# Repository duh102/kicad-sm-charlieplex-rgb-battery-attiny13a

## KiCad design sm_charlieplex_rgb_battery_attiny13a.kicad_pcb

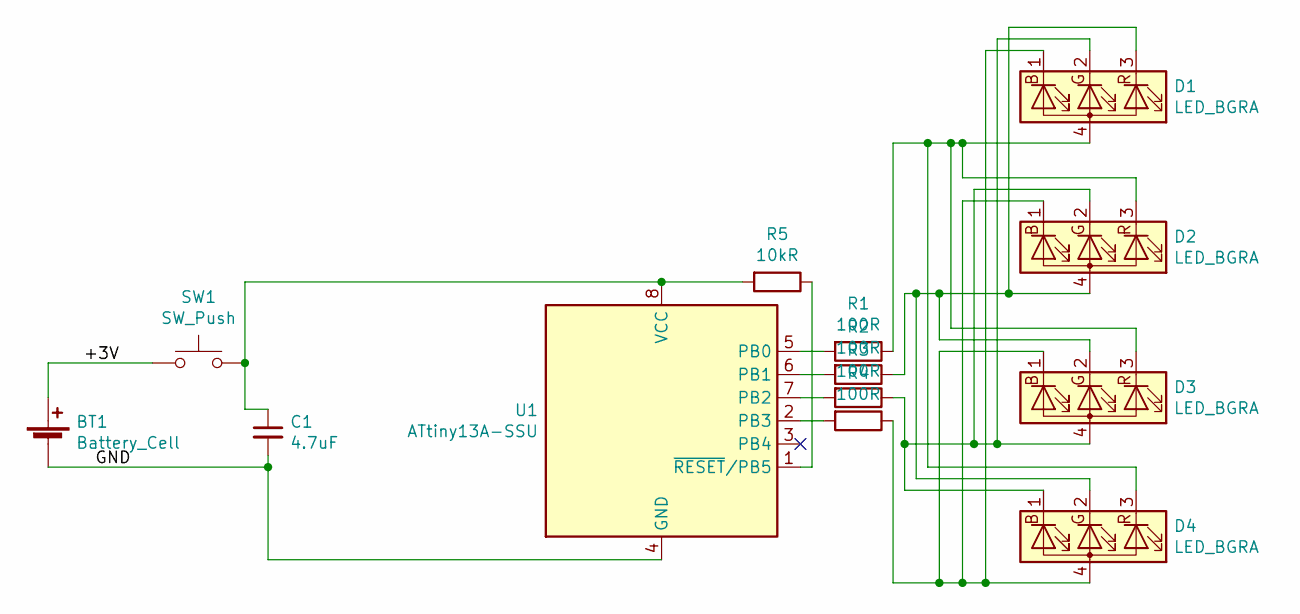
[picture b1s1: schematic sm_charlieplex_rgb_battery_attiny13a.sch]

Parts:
BT1: Battery_Cell; BatteryHolder_Keystone_2998_621_6.8x2.2mm
C1: 4.7uF; C_0805_2012Metric
D1, D2, D3, D4: LED_BGRA; LED_RGB_EAST1616RGBA3
R1, R2, R3, R4: 100R; R_0805_2012Metric
R5: 10kR; R_0805_2012Metric
SW1: SW_Push; SW_Push_2.6x1.6x0.53mm_EVP-BB2A9B000
U1: ATtiny13A-SSU; SOIC-8_3.9x4.9mm_P1.27mm

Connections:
/+3V: BT1.1 (+), SW1.1
/GND: BT1.2 (-), C1.2, U1.4 (GND)
unnamed: C1.1, R5.2, SW1.2, U1.8 (VCC)
unnamed: D1.1 (BK), D2.1 (BK), D3.1 (BK), D4.4 (A), R4.1
unnamed: D1.2 (GK), D2.2 (GK), D3.4 (A), D4.1 (BK), R3.1
unnamed: D1.3 (RK), D2.4 (A), D3.2 (GK), D4.2 (GK), R2.1
unnamed: D1.4 (A), D2.3 (RK), D3.3 (RK), D4.3 (RK), R1.1
unnamed: R1.2, U1.5 (PB0)
unnamed: R2.2, U1.6 (PB1)
unnamed: R3.2, U1.7 (PB2)
unnamed: R4.2, U1.2 (PB3)
unnamed: R5.1, U1.1 (~RESET~/PB5)

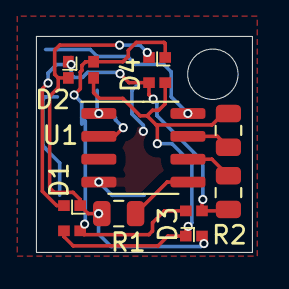
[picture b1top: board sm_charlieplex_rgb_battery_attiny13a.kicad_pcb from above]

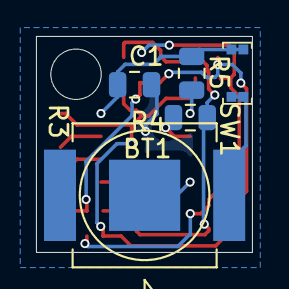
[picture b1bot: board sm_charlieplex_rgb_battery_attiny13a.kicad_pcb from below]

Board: 2 copper layers, 12.0 x 12.0 mm, 13 parts (5 on the bottom side), 12 nets.

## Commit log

2019-12-07 Initial seed commit
2019-12-08 Reformat for attiny13
